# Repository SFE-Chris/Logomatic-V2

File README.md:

Logomatic v2 Serial SD Datalogger (FAT32)
========================================

[  
*Logomatic v2 FAT32(WIG-12772)*](https://www.sparkfun.com/products/12772)

The Logomatic is a great data logger that appears as a flash drive on any operating system. Logs are created
in FAT32 format on the microSD media and can be downloaded quickly over a USB connection by dragging and dropping 
the text files from the device. The board has a built-in RTC and 10 available GPIO pins. 

Repository Contents
-------------------
* **/Firmware** - Firmware that comes pre-installed on the Logomatic
* **/Hardware** - All Eagle design files (.brd, .sch)
* **/Production** - Test bed files and production panel files

Documentation
--------------
* **[Hookup Guide](https://learn.sparkfun.com/tutorials/logomatic-hookup-guide/)** - Basic hookup guide for the Logomatic v2.

Product Versions
----------------
* [WIG-12772](https://www.sparkfun.com/products/12772)- Logomatic v2 with micro-B USB connector and FAT32 programming. 
* *[WIG-10216 (RETIRED)](https://www.sparkfun.com/products/10216)- Logomatic v2 with mini-B USB connector and FAT16 programming.*

License Information
-------------------
The hardware is released under [Creative Commons ShareAlike 4.0 International](https://creativecommons.org/licenses/by-sa/4.0/).
The code is beerware; if you see me (or any other SparkFun employee) at the local, and you've found our code helpful, please buy us a round!

Distributed as-is; no warranty is given.

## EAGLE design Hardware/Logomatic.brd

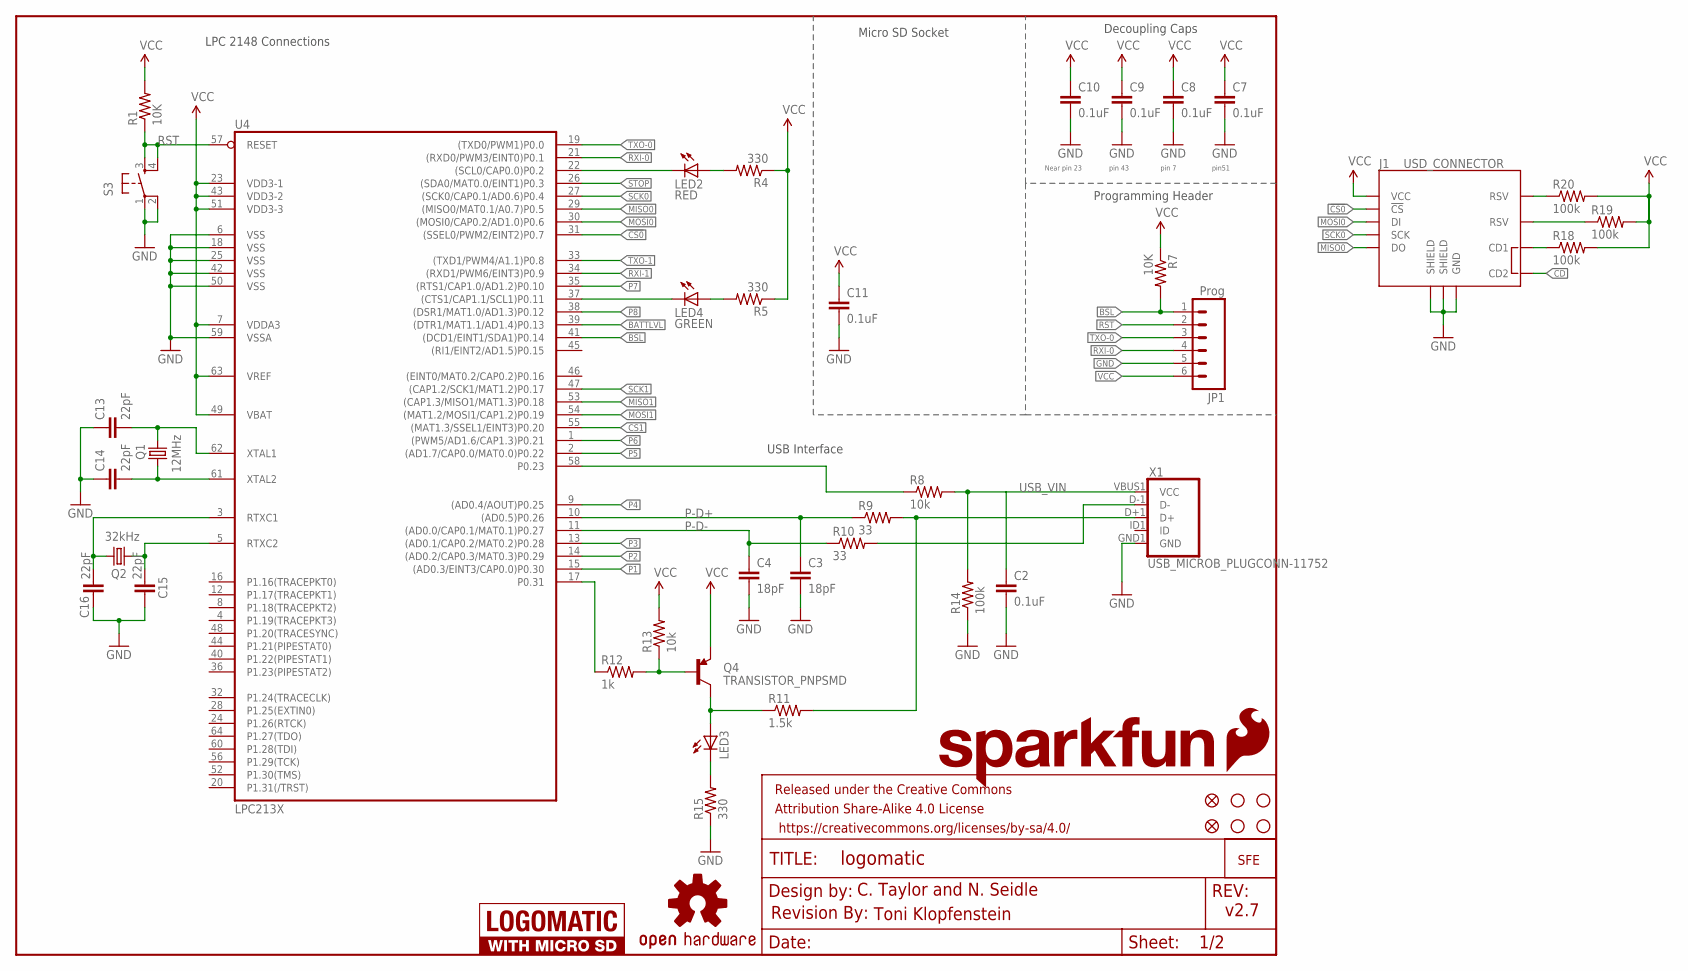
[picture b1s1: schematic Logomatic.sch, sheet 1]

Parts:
C2, C7, C8, C9, C10, C11: 0.1uF; 0603-CAP
C3, C4: 18pF; 0603-CAP
C13, C14, C15, C16: 22pF; 0603-CAP
FRAME2: FRAME-LETTER; CREATIVE_COMMONS
J1: USD_CONNECTOR; MICRO-SD-SOCKET-PP
JP1: Prog; 1X06
LED2: RED; LED-0603
LED3: LED-RED0603; LED-0603
LED4: GREEN; LED-0603
LOGO1: OSHW-LOGOL; OSHW-LOGO-L
LOGO2: SFE_LOGO_NAME.1_INCH; SFE_LOGO_NAME_.1
LOGO3: SFE_LOGO_FLAME.4_INCH; SFE_LOGO_FLAME_.4
Q1: 12MHz; CRYSTAL-SMD-5X3
Q2: 32kHz; CRYSTAL-32KHZ-SMD
Q4: TRANSISTOR_PNPSMD; SOT23-3
R1, R7: 10K; 0603-RES@1
R4, R5, R15: 330; 0603-RES
R8, R13: 10k; 0603-RES@1
R9, R10: 33; 0603-RES
R11: 1.5k; 0603
R12: 1k; 0603-RES@1
R14: 100k; 0603-RES@1
R18, R19, R20: 100k; 0603-RES
S3: Reset; TACTILE_SWITCH_SMD
U4: LPC213X; SQFP-S-10X10-64
U$1, U$2: FIDUCIAL1X2; FIDUCIAL-1X2
U$3, U$4, U$5, U$8: STAND-OFF
U$6: LOGOMATIC_LOGO
U$7: LOGO-SFESK; SFE-LOGO-FLAME
U$10: REVISION
X1: USB_MICROB_PLUGCONN-11752; USB-B-MICRO-SMD_V03

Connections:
!CS0: J1.CS (!CS), U4.31 ((SSEL0/PWM2/EINT2)P0.7)
BATTLVL: U4.39 ((DTR1/MAT1.1/AD1.4)P0.13); also elsewhere on the board
BSL: JP1.1, R7.2, U4.41 ((DCD1/EINT1/SDA1)P0.14)
CD: J1.CD2
CS1: U4.55 ((MAT1.3/SSEL1/EINT3)P0.20); also elsewhere on the board
GND: C2.2, C3.2, C4.2, C7.2, C8.2, C9.2, C10.2, C11.2, C13.1, C14.1, C15.1, C16.1, J1.GND, J1.GND1 (SHIELD), J1.GND3 (SHIELD), JP1.5, R14.1, R15.1, S3.1, S3.2, U4.6 (VSS), U4.18 (VSS), U4.25 (VSS), U4.42 (VSS), U4.50 (VSS), U4.59 (VSSA), X1.GND1 (GND); also elsewhere on the board
MISO0: J1.DO, U4.29 ((MISO0/MAT0.1/A0.7)P0.5)
MISO1: U4.53 ((CAP1.3/MISO1/MAT1.3)P0.18); also elsewhere on the board
MOSI0: J1.DI, U4.30 ((MOSI0/CAP0.2/AD1.0)P0.6)
MOSI1: U4.54 ((MAT1.2/MOSI1/CAP1.2)P0.19); also elsewhere on the board
unnamed: J1.CD1, R18.1
unnamed: J1.RSV1 (RSV), R20.1
unnamed: C13.2, Q1.3 (2), U4.62 (XTAL1)
unnamed: C16.2, Q2.X2 (2), U4.3 (RTXC1)
unnamed: LED2.A, R4.2
unnamed: C15.2, Q2.X1 (1), U4.5 (RTXC2)
unnamed: J1.RSV2 (RSV), R19.1
unnamed: R8.1, U4.58 (P0.23)
unnamed: Q4.1 (B), R12.2, R13.1
unnamed: LED4.A, R5.2
unnamed: C14.2, Q1.1, U4.61 (XTAL2)
unnamed: R12.1, U4.17 (P0.31)
unnamed: LED3.C, R15.2
P1: U4.15 ((AD0.3/EINT3/CAP0.0)P0.30); also elsewhere on the board
P2: U4.14 ((AD0.2/CAP0.3/MAT0.3)P0.29); also elsewhere on the board
P3: U4.13 ((AD0.1/CAP0.2/MAT0.2)P0.28); also elsewhere on the board
P4: U4.9 ((AD0.4/AOUT)P0.25); also elsewhere on the board
P5: U4.2 ((AD1.7/CAP0.0/MAT0.0)P0.22); also elsewhere on the board
P6: U4.1 ((PWM5/AD1.6/CAP1.3)P0.21); also elsewhere on the board
P7: U4.35 ((RTS1/CAP1.0/AD1.2)P0.10); also elsewhere on the board
P8: U4.38 ((DSR1/MAT1.0/AD1.3)P0.12); also elsewhere on the board
P-D+: C3.1, R9.1, U4.10 ((AD0.5)P0.26)
P-D-: C4.1, R10.1, U4.11 ((AD0.0/CAP0.1/MAT0.1)P0.27)
RST: JP1.2, R1.1, S3.3, S3.4, U4.57 (RESET)
RXI-0: JP1.4, U4.21 ((RXD0/PWM3/EINT0)P0.1)
RXI-1: U4.34 ((RXD1/PWM6/EINT3)P0.9); also elsewhere on the board
SCK0: J1.SCLK (SCK), U4.27 ((SCK0/CAP0.1/AD0.6)P0.4)
SCK1: U4.47 ((CAP1.2/SCK1/MAT1.2)P0.17); also elsewhere on the board
STAT: LED3.A, Q4.3 (C), R11.1
STAT0: LED2.C, U4.22 ((SCL0/CAP0.0)P0.2)
STAT1: LED4.C, U4.37 ((CTS1/CAP1.1/SCL1)P0.11)
STOP: U4.26 ((SDA0/MAT0.0/EINT1)P0.3); also elsewhere on the board
TXO-0: JP1.3, U4.19 ((TXD0/PWM1)P0.0)
TXO-1: U4.33 ((TXD1/PWM4/A1.1)P0.8); also elsewhere on the board
USB_D+: R9.2, R11.2, X1.D+1 (D+)
USB_D-: R10.2, X1.D-1 (D-)
USB_VIN: C2.1, R8.2, R14.2, X1.VBUS1 (VCC); also elsewhere on the board
VCC: C7.1, C8.1, C9.1, C10.1, C11.1, J1.VCC, JP1.6, Q4.2 (E), R1.2, R4.1, R5.1, R7.1, R13.2, R18.2, R19.2, R20.2, U4.7 (VDDA3), U4.23 (VDD3-1), U4.43 (VDD3-2), U4.49 (VBAT), U4.51 (VDD3-3), U4.63 (VREF); also elsewhere on the board

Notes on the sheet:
Near pin 23
pin 43
pin51
Decoupling Caps
Programming Header
USB Interface
Micro SD Socket
pin 7
LPC 2148 Connections
C. Taylor and N. Seidle
Toni Klopfenstein
v2.7

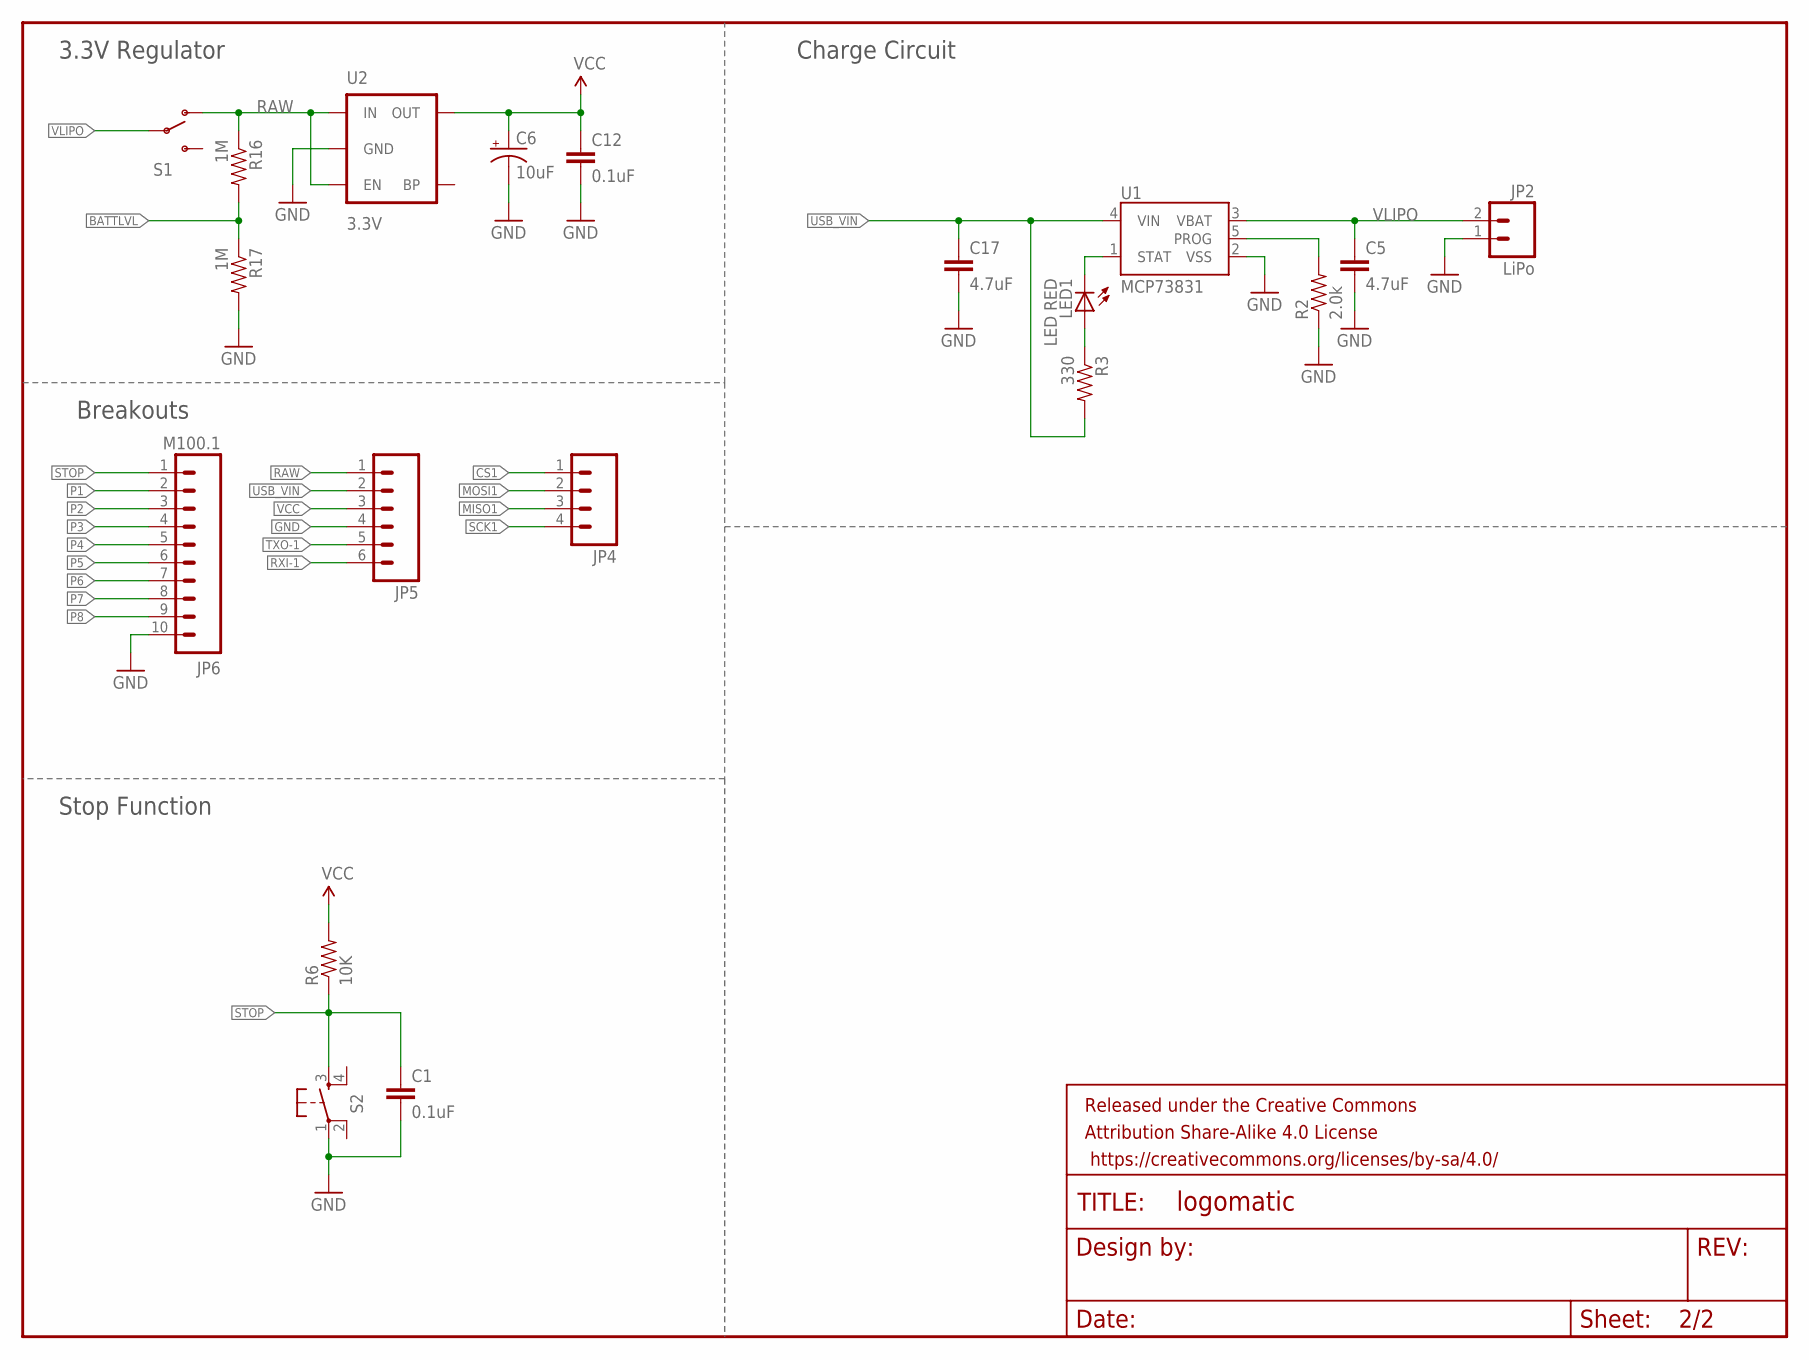
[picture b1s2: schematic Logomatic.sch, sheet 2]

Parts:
C1, C12: 0.1uF; 0603-CAP
C5, C17: 4.7uF; 0603-CAP
C6: 10uF; EIA3216
FRAME4: FRAME-LETTER; CREATIVE_COMMONS
JP2: LiPo; JST-2-SMD
JP4: M04PTH; 1X04
JP5: M06SIP; 1X06
JP6: M100.1; 1X10
LED1: LED RED; LED-0603
R2: 2.0k; 0603-RES
R3: 330; 0603-RES
R6: 10K; 0603-RES@1
R16, R17: 1M; 0603-RES@1
S1: SWITCH-SPSTSMD; AYZ0202
S2: Stop; TACTILE_SWITCH_SMD
U1: MCP73831; SOT23-5
U2: 3.3V; SOT23-5

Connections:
BATTLVL: R16.2, R17.1; also elsewhere on the board
CS1: JP4.1; also elsewhere on the board
GND: C1.2, C5.2, C6.C (-), C12.2, C17.2, JP2.1, JP5.4, JP6.10, R2.1, R17.2, S2.1, U1.2 (VSS), U2.2 (GND); also elsewhere on the board
MISO1: JP4.3; also elsewhere on the board
MOSI1: JP4.2; also elsewhere on the board
unnamed: R2.2, U1.5 (PROG)
unnamed: LED1.C, U1.1 (STAT)
unnamed: LED1.A, R3.1
P1: JP6.2; also elsewhere on the board
P2: JP6.3; also elsewhere on the board
P3: JP6.4; also elsewhere on the board
P4: JP6.5; also elsewhere on the board
P5: JP6.6; also elsewhere on the board
P6: JP6.7; also elsewhere on the board
P7: JP6.8; also elsewhere on the board
P8: JP6.9; also elsewhere on the board
RAW: JP5.1, R16.1, S1.1 (O), U2.1 (IN), U2.3 (EN)
RXI-1: JP5.6; also elsewhere on the board
SCK1: JP4.4; also elsewhere on the board
STOP: C1.1, JP6.1, R6.1, S2.3; also elsewhere on the board
TXO-1: JP5.5; also elsewhere on the board
USB_VIN: C17.1, JP5.2, R3.2, U1.4 (VIN); also elsewhere on the board
VCC: C6.A (+), C12.1, JP5.3, R6.2, U2.5 (OUT); also elsewhere on the board
VLIPO: C5.1, JP2.2, S1.2, U1.3 (VBAT)

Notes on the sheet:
3.3V Regulator
Charge Circuit
Breakouts
Stop Function

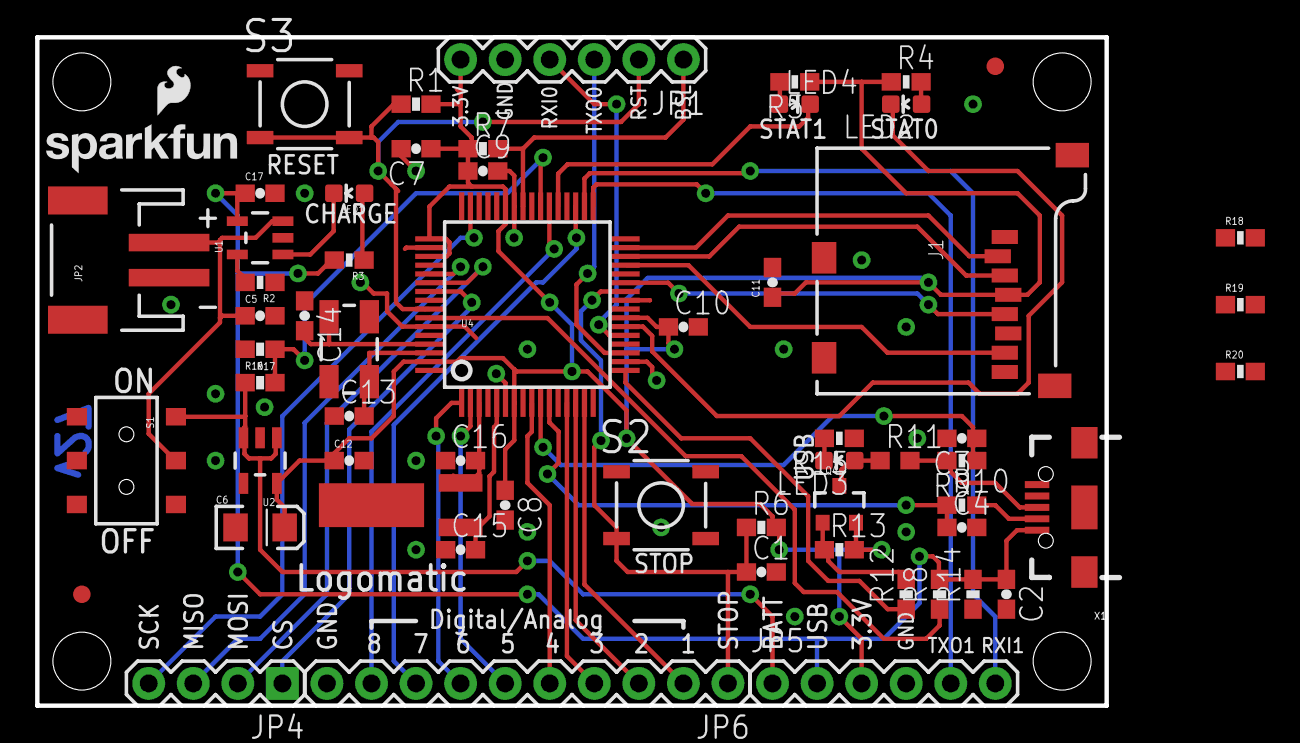
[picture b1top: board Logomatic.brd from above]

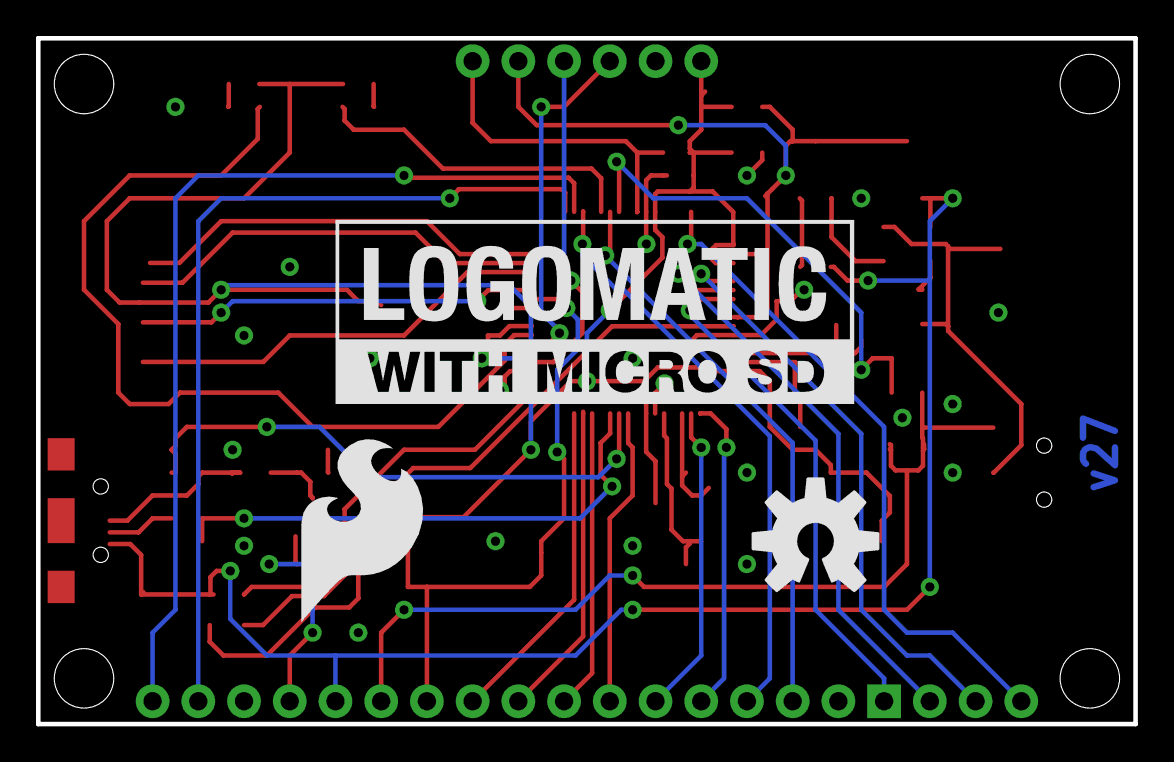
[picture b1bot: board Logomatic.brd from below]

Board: 2 copper layers, 61.0 x 38.1 mm, 71 parts (3 on the bottom side), 52 nets.

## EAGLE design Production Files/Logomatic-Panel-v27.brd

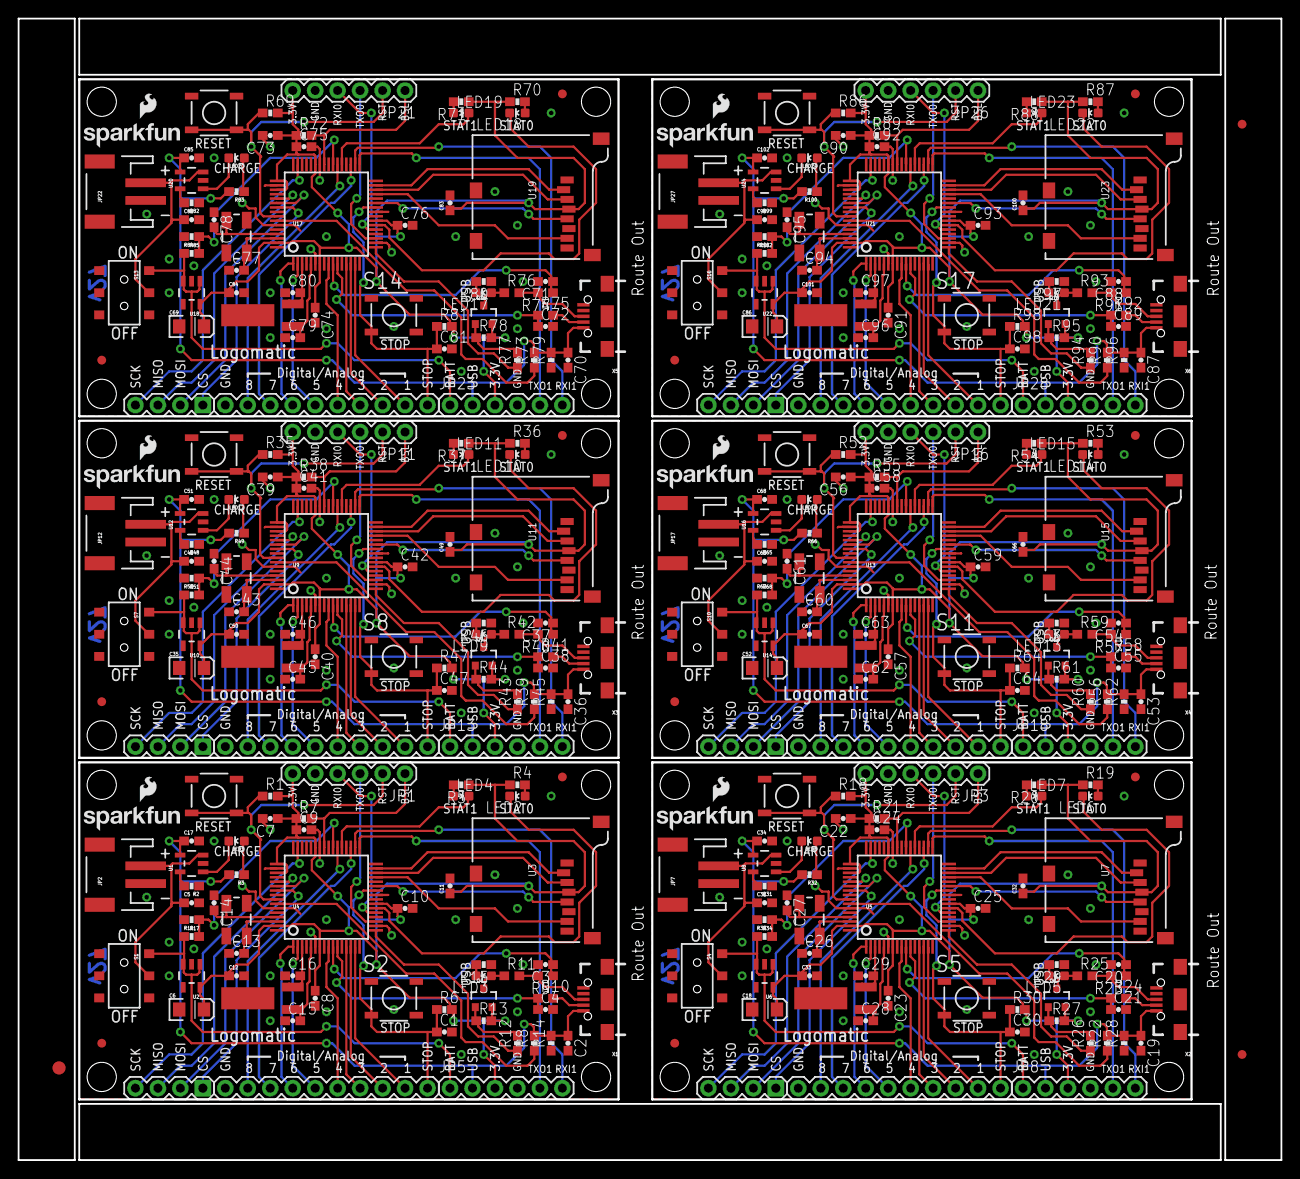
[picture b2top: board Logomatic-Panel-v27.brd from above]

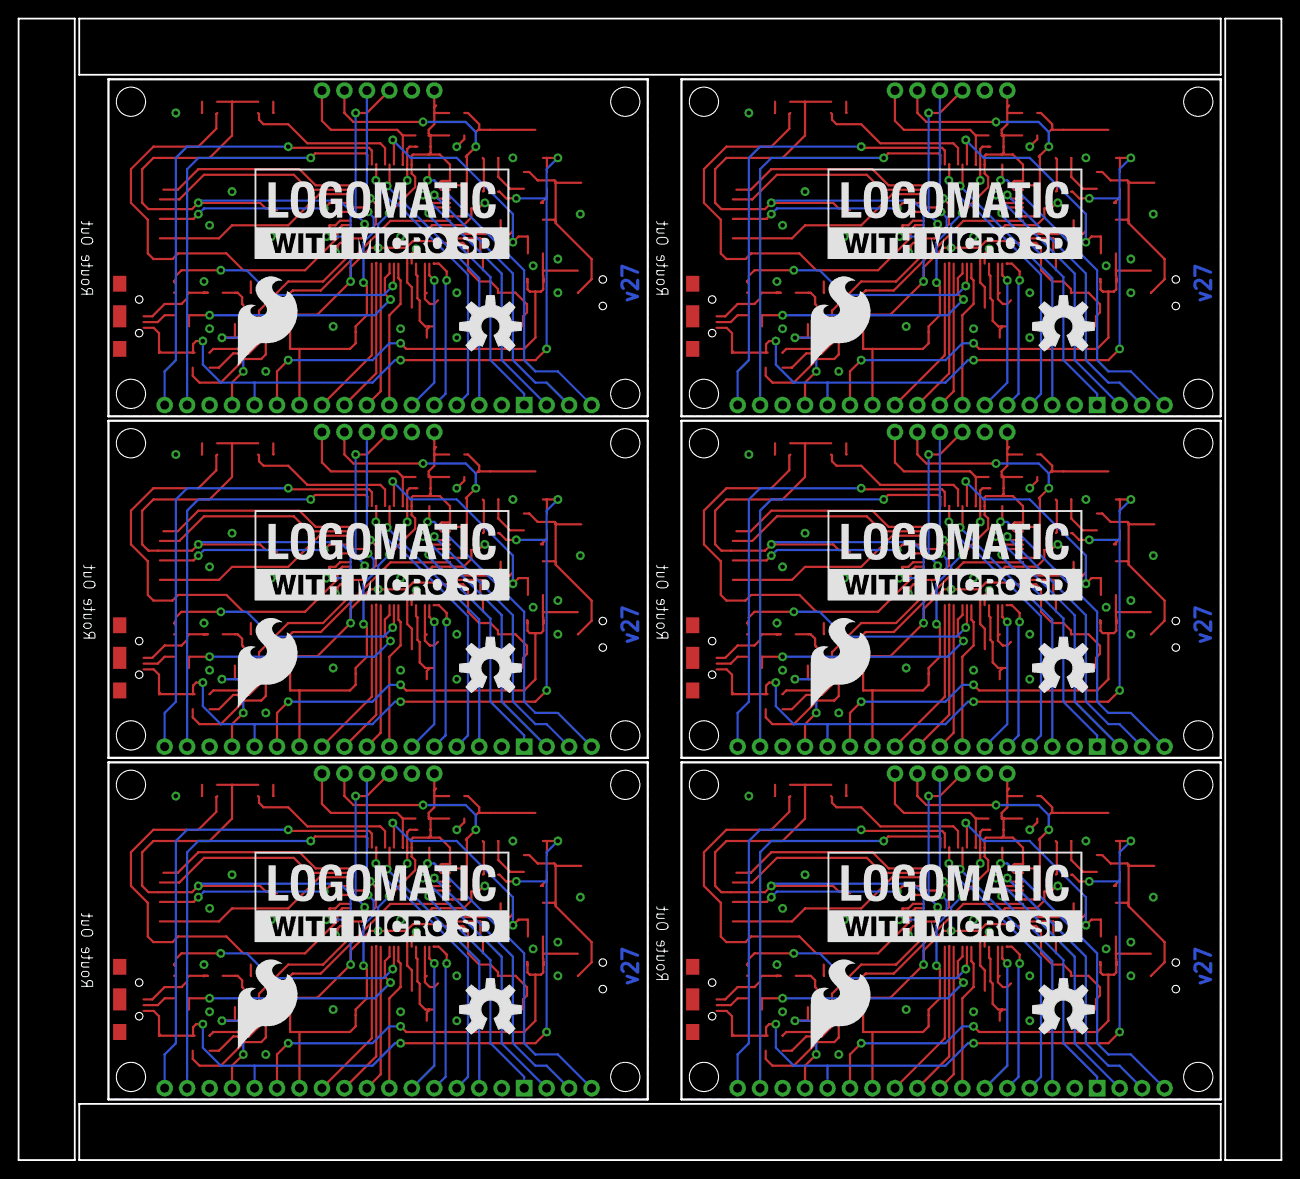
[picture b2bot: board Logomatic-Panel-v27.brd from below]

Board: 2 copper layers, 142.7 x 129.0 mm, 393 parts (18 on the bottom side), 294 nets.

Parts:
C1, C2, C7, C8, C9, C10, C11, C12, C19, C22, C23, C24, C25, C30, C32, C33, C36, C39, C40, C41, C42, C47, C49, C50, C53, C56, C57, C58, C59, C64, C66, C67, C70, C73, C74, C75, C76, C81, C83, C84, C87, C90, C91, C92, C93, C98, C100, C101: 0.1uF; 0603-CAP
C3, C4, C20, C21, C37, C38, C54, C55, C71, C72, C88, C89: 18pF; 0603-CAP
C5, C17, C31, C34, C48, C51, C65, C68, C82, C85, C99, C102: 4.7uF; 0603-CAP
C6, C18, C35, C52, C69, C86: 10uF; EIA3216
C13, C14, C15, C16, C26, C27, C28, C29, C43, C44, C45, C46, C60, C61, C62, C63, C77, C78, C79, C80, C94, C95, C96, C97: 22pF; 0603-CAP
E$1, E$2: FIDUCIAL-1X2
E$3: FIDUCIAL-1.5X3
JP1, JP3, JP11, JP16, JP21, JP26: Prog; 1X06
JP2, JP7, JP12, JP17, JP22, JP27: LiPo; JST-2-SMD
JP4, JP9, JP14, JP19, JP24, JP29: 1X04
JP5, JP8, JP13, JP18, JP23, JP28: 1X06
JP6, JP10, JP15, JP20, JP25, JP30: M100.1; 1X10
LED1, LED8, LED12, LED16, LED20, LED24: LED RED; LED-0603
LED2, LED6, LED10, LED14, LED18, LED22: RED; LED-0603
LED3, LED5, LED9, LED13, LED17, LED21: LED-0603
LED4, LED7, LED11, LED15, LED19, LED23: GREEN; LED-0603
LOGO1, LOGO4, LOGO7, LOGO10, LOGO13, LOGO16: OSHW-LOGOL; OSHW-LOGO-L
LOGO2, LOGO5, LOGO8, LOGO11, LOGO14, LOGO17: SFE_LOGO_NAME.1_INCH; SFE_LOGO_NAME_.1
LOGO3, LOGO6, LOGO9, LOGO12, LOGO15, LOGO18: SFE_LOGO_FLAME.4_INCH; SFE_LOGO_FLAME_.4
Q1, Q3, Q7, Q10, Q13, Q16: 12MHz; CRYSTAL-SMD-5X3
Q2, Q5, Q8, Q11, Q14, Q17: 32kHz; CRYSTAL-32KHZ-SMD
Q4, Q6, Q9, Q12, Q15, Q18: TRANSISTOR_PNPSMD; SOT23-3
R1, R6, R7, R18, R21, R30, R35, R38, R47, R52, R55, R64, R69, R72, R81, R86, R89, R98: 10K; 0603-RES
R2, R31, R48, R65, R82, R99: 2K; 0603-RES
R3, R4, R5, R15, R19, R20, R29, R32, R36, R37, R46, R49, R53, R54, R63, R66, R70, R71, R80, R83, R87, R88, R97, R100: 330; 0603-RES
R8, R13, R22, R27, R39, R44, R56, R61, R73, R78, R90, R95: 10k; 0603-RES
R9, R10, R23, R24, R40, R41, R57, R58, R74, R75, R91, R92: 33; 0603
R11, R25, R42, R59, R76, R93: 1.5k; 0603
R12, R26, R43, R60, R77, R94: 1k; 0603-RES
R14, R28, R45, R62, R79, R96: 100k; 0603-RES
R16, R17, R33, R34, R50, R51, R67, R68, R84, R85, R101, R102: 1M; 0603-RES
S1, S4, S7, S10, S13, S16: AYZ0202
S2, S5, S8, S11, S14, S17: Stop; TACTILE_SWITCH_SMD
S3, S6, S9, S12, S15, S18: Reset; TACTILE_SWITCH_SMD
U1, U8, U12, U16, U20, U24: MCP73831; SOT23-5
U2, U6, U10, U14, U18, U22: 3.3V; SOT23-5
U3, U7, U11, U15, U19, U23: USD-SOCKETNEW; MICRO-SD-SOCKET-PP
U4, U5, U9, U13, U17, U21: LPC213X; SQFP-S-10X10-64
U$1, U$2, U$9, U$10, U$17, U$18, U$25, U$26, U$33, U$34, U$41, U$42: FIDUCIAL1X2; FIDUCIAL-1X2
U$3, U$4, U$5, U$8, U$11, U$12, U$13, U$14, U$19, U$20, U$21, U$22, U$27, U$28, U$29, U$30, U$35, U$36, U$37, U$38, U$43, U$44, U$45, U$46: STAND-OFF
U$6, U$16, U$24, U$32, U$40, U$48: LOGOMATIC_LOGO
U$7, U$15, U$23, U$31, U$39, U$47: LOGO-SFESK; SFE-LOGO-FLAME
X1, X2, X3, X4, X5, X6: USB_MICROB_PLUGCONN-11752; USB-B-MICRO-SMD_V03

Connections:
BATTLVL: R16.2, R17.1, U4.39
BATTLVL1: R33.2, R34.1, U5.39
BATTLVL2: R50.2, R51.1, U9.39
BATTLVL3: R67.2, R68.1, U13.39
BATTLVL4: R84.2, R85.1, U17.39
BATTLVL5: R101.2, R102.1, U21.39
BSL: JP1.1, R7.2, U4.41
BSL1: JP3.1, R21.2, U5.41
BSL2: JP11.1, R38.2, U9.41
BSL3: JP16.1, R55.2, U13.41
BSL4: JP21.1, R72.2, U17.41
BSL5: JP26.1, R89.2, U21.41
CS0: U3.2, U4.31
CS1: JP4.1, U4.55
CS2: U5.31, U7.2
CS3: JP9.1, U5.55
CS4: U9.31, U11.2
CS5: JP14.1, U9.55
CS6: U13.31, U15.2
CS7: JP19.1, U13.55
CS8: U17.31, U19.2
CS9: JP24.1, U17.55
CS10: U21.31, U23.2
CS11: JP29.1, U21.55
GND: C1.2, C2.2, C3.2, C4.2, C5.2, C6.C, C7.2, C8.2, C9.2, C10.2, C11.2, C12.2, C13.1, C14.1, C15.1, C16.1, C17.2, JP1.5, JP2.1, JP5.4, JP6.10, R2.1, R14.1, R15.1, R17.2, S2.1, S3.1, S3.2, U1.2, U2.2, U3.6, U3.CD2, U3.GND1, U4.6, U4.18, U4.25, U4.42, U4.50, U4.59, X1.GND1
GND1: C18.C, C19.2, C20.2, C21.2, C22.2, C23.2, C24.2, C25.2, C26.1, C27.1, C28.1, C29.1, C30.2, C31.2, C32.2, C33.2, C34.2, JP3.5, JP7.1, JP8.4, JP10.10, R28.1, R29.1, R31.1, R34.2, S5.1, S6.1, S6.2, U5.6, U5.18, U5.25, U5.42, U5.50, U5.59, U6.2, U7.6, U7.CD2, U7.GND1, U8.2, X2.GND1
GND2: C35.C, C36.2, C37.2, C38.2, C39.2, C40.2, C41.2, C42.2, C43.1, C44.1, C45.1, C46.1, C47.2, C48.2, C49.2, C50.2, C51.2, JP11.5, JP12.1, JP13.4, JP15.10, R45.1, R46.1, R48.1, R51.2, S8.1, S9.1, S9.2, U9.6, U9.18, U9.25, U9.42, U9.50, U9.59, U10.2, U11.6, U11.CD2, U11.GND1, U12.2, X3.GND1
GND3: C52.C, C53.2, C54.2, C55.2, C56.2, C57.2, C58.2, C59.2, C60.1, C61.1, C62.1, C63.1, C64.2, C65.2, C66.2, C67.2, C68.2, JP16.5, JP17.1, JP18.4, JP20.10, R62.1, R63.1, R65.1, R68.2, S11.1, S12.1, S12.2, U13.6, U13.18, U13.25, U13.42, U13.50, U13.59, U14.2, U15.6, U15.CD2, U15.GND1, U16.2, X4.GND1
GND4: C69.C, C70.2, C71.2, C72.2, C73.2, C74.2, C75.2, C76.2, C77.1, C78.1, C79.1, C80.1, C81.2, C82.2, C83.2, C84.2, C85.2, JP21.5, JP22.1, JP23.4, JP25.10, R79.1, R80.1, R82.1, R85.2, S14.1, S15.1, S15.2, U17.6, U17.18, U17.25, U17.42, U17.50, U17.59, U18.2, U19.6, U19.CD2, U19.GND1, U20.2, X5.GND1
GND5: C86.C, C87.2, C88.2, C89.2, C90.2, C91.2, C92.2, C93.2, C94.1, C95.1, C96.1, C97.1, C98.2, C99.2, C100.2, C101.2, C102.2, JP26.5, JP27.1, JP28.4, JP30.10, R96.1, R97.1, R99.1, R102.2, S17.1, S18.1, S18.2, U21.6, U21.18, U21.25, U21.42, U21.50, U21.59, U22.2, U23.6, U23.CD2, U23.GND1, U24.2, X6.GND1
MISO0: U3.7, U4.29
MISO1: JP4.3, U4.53
MISO2: U5.29, U7.7
MISO3: JP9.3, U5.53
MISO4: U9.29, U11.7
MISO5: JP14.3, U9.53
MISO6: U13.29, U15.7
MISO7: JP19.3, U13.53
MISO8: U17.29, U19.7
MISO9: JP24.3, U17.53
MISO10: U21.29, U23.7
MISO11: JP29.3, U21.53
MOSI0: U3.3, U4.30
MOSI1: JP4.2, U4.54
MOSI2: U5.30, U7.3
MOSI3: JP9.2, U5.54
MOSI4: U9.30, U11.3
MOSI5: JP14.2, U9.54
MOSI6: U13.30, U15.3
MOSI7: JP19.2, U13.54
MOSI8: U17.30, U19.3
MOSI9: JP24.2, U17.54
MOSI10: U21.30, U23.3
MOSI11: JP29.2, U21.54
unnamed: R2.2, U1.5
unnamed: R22.1, U5.58
unnamed: Q6.1, R26.2, R27.1
unnamed: R26.1, U5.17
unnamed: C13.2, Q1.3, U4.62
unnamed: C16.2, Q2.X2, U4.3
unnamed: LED2.A, R4.2
unnamed: LED5.C, R29.2
unnamed: C15.2, Q2.X1, U4.5
unnamed: LED6.A, R19.2
unnamed: LED7.A, R20.2
unnamed: LED1.C, U1.1
unnamed: LED1.A, R3.1
unnamed: C26.2, Q3.3, U5.62
unnamed: C27.2, Q3.1, U5.61
unnamed: R8.1, U4.58
unnamed: Q4.1, R12.2, R13.1
unnamed: C29.2, Q5.X2, U5.3
unnamed: LED4.A, R5.2
unnamed: C28.2, Q5.X1, U5.5
unnamed: C14.2, Q1.1, U4.61
unnamed: LED8.C, U8.1
unnamed: LED8.A, R32.1
unnamed: R31.2, U8.5
unnamed: R39.1, U9.58
unnamed: Q9.1, R43.2, R44.1
unnamed: R43.1, U9.17
unnamed: LED9.C, R46.2
unnamed: LED10.A, R36.2
unnamed: LED11.A, R37.2
unnamed: R12.1, U4.17
unnamed: C43.2, Q7.3, U9.62
unnamed: LED3.C, R15.2
unnamed: C44.2, Q7.1, U9.61
unnamed: C46.2, Q8.X2, U9.3
unnamed: C45.2, Q8.X1, U9.5
unnamed: LED12.C, U12.1
unnamed: LED12.A, R49.1
unnamed: R48.2, U12.5
unnamed: R56.1, U13.58
unnamed: Q12.1, R60.2, R61.1
unnamed: R60.1, U13.17
unnamed: LED13.C, R63.2
unnamed: LED14.A, R53.2
unnamed: LED15.A, R54.2
unnamed: C60.2, Q10.3, U13.62
unnamed: C61.2, Q10.1, U13.61
unnamed: C63.2, Q11.X2, U13.3
unnamed: C62.2, Q11.X1, U13.5
unnamed: LED16.C, U16.1
unnamed: LED16.A, R66.1
unnamed: R65.2, U16.5
unnamed: R73.1, U17.58
unnamed: Q15.1, R77.2, R78.1
unnamed: R77.1, U17.17
unnamed: LED17.C, R80.2
unnamed: LED18.A, R70.2
unnamed: LED19.A, R71.2
unnamed: C77.2, Q13.3, U17.62
unnamed: C78.2, Q13.1, U17.61
unnamed: C80.2, Q14.X2, U17.3
unnamed: C79.2, Q14.X1, U17.5
unnamed: LED20.C, U20.1
unnamed: LED20.A, R83.1
unnamed: R82.2, U20.5
unnamed: R90.1, U21.58
unnamed: Q18.1, R94.2, R95.1
unnamed: R94.1, U21.17
unnamed: LED21.C, R97.2
unnamed: LED22.A, R87.2
unnamed: LED23.A, R88.2
unnamed: C94.2, Q16.3, U21.62
unnamed: C95.2, Q16.1, U21.61
unnamed: C97.2, Q17.X2, U21.3
unnamed: C96.2, Q17.X1, U21.5
unnamed: LED24.C, U24.1
unnamed: LED24.A, R100.1
unnamed: R99.2, U24.5
P1: JP6.2, U4.15
P2: JP6.3, U4.14
P3: JP6.4, U4.13
P4: JP6.5, U4.9
P5: JP6.6, U4.2
P6: JP6.7, U4.1
P7: JP6.8, U4.35
P8: JP6.9, U4.38
P9: JP10.5, U5.9
P10: JP10.4, U5.13
P11: JP10.3, U5.14
P12: JP10.2, U5.15
P13: JP10.8, U5.35
P14: JP10.9, U5.38
P15: JP10.7, U5.1
P16: JP10.6, U5.2
P17: JP15.5, U9.9
P18: JP15.4, U9.13
P19: JP15.3, U9.14
P20: JP15.2, U9.15
P21: JP15.8, U9.35
P22: JP15.9, U9.38
P23: JP15.7, U9.1
P24: JP15.6, U9.2
P25: JP20.5, U13.9
P26: JP20.4, U13.13
P27: JP20.3, U13.14
P28: JP20.2, U13.15
P29: JP20.8, U13.35
P30: JP20.9, U13.38
P31: JP20.7, U13.1
P32: JP20.6, U13.2
P33: JP25.5, U17.9
P34: JP25.4, U17.13
P35: JP25.3, U17.14
P36: JP25.2, U17.15
P37: JP25.8, U17.35
P38: JP25.9, U17.38
P39: JP25.7, U17.1
P40: JP25.6, U17.2
P41: JP30.5, U21.9
P42: JP30.4, U21.13
P43: JP30.3, U21.14
P44: JP30.2, U21.15
P45: JP30.8, U21.35
P46: JP30.9, U21.38
P47: JP30.7, U21.1
P48: JP30.6, U21.2
P-D+: C3.1, R9.1, U4.10
P-D+1: C20.1, R23.1, U5.10
P-D+2: C37.1, R40.1, U9.10
P-D+3: C54.1, R57.1, U13.10
P-D+4: C71.1, R74.1, U17.10
P-D+5: C88.1, R91.1, U21.10
P-D-: C4.1, R10.1, U4.11
P-D-1: C21.1, R24.1, U5.11
P-D-2: C38.1, R41.1, U9.11
P-D-3: C55.1, R58.1, U13.11
P-D-4: C72.1, R75.1, U17.11
P-D-5: C89.1, R92.1, U21.11
RAW: JP5.1, R16.1, S1.1, U2.1, U2.3
RAW1: JP8.1, R33.1, S4.1, U6.1, U6.3
RAW2: JP13.1, R50.1, S7.1, U10.1, U10.3
RAW3: JP18.1, R67.1, S10.1, U14.1, U14.3
RAW4: JP23.1, R84.1, S13.1, U18.1, U18.3
RAW5: JP28.1, R101.1, S16.1, U22.1, U22.3
RST: JP1.2, R1.1, S3.3, S3.4, U4.57
RST1: JP3.2, R18.1, S6.3, S6.4, U5.57
RST2: JP11.2, R35.1, S9.3, S9.4, U9.57
RST3: JP16.2, R52.1, S12.3, S12.4, U13.57
RST4: JP21.2, R69.1, S15.3, S15.4, U17.57
RST5: JP26.2, R86.1, S18.3, S18.4, U21.57
RXI-0: JP1.4, U4.21
RXI-1: JP5.6, U4.34
RXI-2: JP3.4, U5.21
RXI-3: JP8.6, U5.34
RXI-4: JP11.4, U9.21
RXI-5: JP13.6, U9.34
RXI-6: JP16.4, U13.21
RXI-7: JP18.6, U13.34
RXI-8: JP21.4, U17.21
RXI-9: JP23.6, U17.34
RXI-10: JP26.4, U21.21
RXI-11: JP28.6, U21.34
SCK0: U3.5, U4.27
SCK1: JP4.4, U4.47
SCK2: U5.27, U7.5
SCK3: JP9.4, U5.47
SCK4: U9.27, U11.5
SCK5: JP14.4, U9.47
SCK6: U13.27, U15.5
SCK7: JP19.4, U13.47
SCK8: U17.27, U19.5
SCK9: JP24.4, U17.47
SCK10: U21.27, U23.5
SCK11: JP29.4, U21.47
STAT: LED3.A, Q4.3, R11.1
STAT0: LED2.C, U4.22
STAT1: LED4.C, U4.37
STAT2: LED6.C, U5.22
STAT3: LED7.C, U5.37
STAT4: LED5.A, Q6.3, R25.1
STAT5: LED10.C, U9.22
STAT6: LED11.C, U9.37
STAT7: LED9.A, Q9.3, R42.1
STAT8: LED14.C, U13.22
STAT9: LED15.C, U13.37
STAT10: LED13.A, Q12.3, R59.1
STAT11: LED18.C, U17.22
STAT12: LED19.C, U17.37
STAT13: LED17.A, Q15.3, R76.1
STAT14: LED22.C, U21.22
STAT15: LED23.C, U21.37
STAT16: LED21.A, Q18.3, R93.1
STOP: C1.1, JP6.1, R6.1, S2.3, U4.26
STOP1: C30.1, JP10.1, R30.1, S5.3, U5.26
STOP2: C47.1, JP15.1, R47.1, S8.3, U9.26
STOP3: C64.1, JP20.1, R64.1, S11.3, U13.26
STOP4: C81.1, JP25.1, R81.1, S14.3, U17.26
STOP5: C98.1, JP30.1, R98.1, S17.3, U21.26
TXO-0: JP1.3, U4.19
TXO-1: JP5.5, U4.33
TXO-2: JP3.3, U5.19
TXO-3: JP8.5, U5.33
TXO-4: JP11.3, U9.19
TXO-5: JP13.5, U9.33
TXO-6: JP16.3, U13.19
TXO-7: JP18.5, U13.33
TXO-8: JP21.3, U17.19
TXO-9: JP23.5, U17.33
TXO-10: JP26.3, U21.19
TXO-11: JP28.5, U21.33
USB_D+: R9.2, R11.2, X1.D+1
USB_D+1: R23.2, R25.2, X2.D+1
USB_D+2: R40.2, R42.2, X3.D+1
USB_D+3: R57.2, R59.2, X4.D+1
USB_D+4: R74.2, R76.2, X5.D+1
USB_D+5: R91.2, R93.2, X6.D+1
USB_D-: R10.2, X1.D-1
USB_D-1: R24.2, X2.D-1
USB_D-2: R41.2, X3.D-1
USB_D-3: R58.2, X4.D-1
USB_D-4: R75.2, X5.D-1
USB_D-5: R92.2, X6.D-1
USB_VIN: C2.1, C17.1, JP5.2, R3.2, R8.2, R14.2, U1.4, X1.VBUS1
USB_VIN1: C19.1, C34.1, JP8.2, R22.2, R28.2, R32.2, U8.4, X2.VBUS1
USB_VIN2: C36.1, C51.1, JP13.2, R39.2, R45.2, R49.2, U12.4, X3.VBUS1
USB_VIN3: C53.1, C68.1, JP18.2, R56.2, R62.2, R66.2, U16.4, X4.VBUS1
USB_VIN4: C70.1, C85.1, JP23.2, R73.2, R79.2, R83.2, U20.4, X5.VBUS1
USB_VIN5: C87.1, C102.1, JP28.2, R90.2, R96.2, R100.2, U24.4, X6.VBUS1
VCC: C6.A, C7.1, C8.1, C9.1, C10.1, C11.1, C12.1, JP1.6, JP5.3, Q4.2, R1.2, R4.1, R5.1, R6.2, R7.1, R13.2, U2.5, U3.4, U4.7, U4.23, U4.43, U4.49, U4.51, U4.63
VCC1: C18.A, C22.1, C23.1, C24.1, C25.1, C32.1, C33.1, JP3.6, JP8.3, Q6.2, R18.2, R19.1, R20.1, R21.1, R27.2, R30.2, U5.7, U5.23, U5.43, U5.49, U5.51, U5.63, U6.5, U7.4
VCC2: C35.A, C39.1, C40.1, C41.1, C42.1, C49.1, C50.1, JP11.6, JP13.3, Q9.2, R35.2, R36.1, R37.1, R38.1, R44.2, R47.2, U9.7, U9.23, U9.43, U9.49, U9.51, U9.63, U10.5, U11.4
VCC3: C52.A, C56.1, C57.1, C58.1, C59.1, C66.1, C67.1, JP16.6, JP18.3, Q12.2, R52.2, R53.1, R54.1, R55.1, R61.2, R64.2, U13.7, U13.23, U13.43, U13.49, U13.51, U13.63, U14.5, U15.4
VCC4: C69.A, C73.1, C74.1, C75.1, C76.1, C83.1, C84.1, JP21.6, JP23.3, Q15.2, R69.2, R70.1, R71.1, R72.1, R78.2, R81.2, U17.7, U17.23, U17.43, U17.49, U17.51, U17.63, U18.5, U19.4
VCC5: C86.A, C90.1, C91.1, C92.1, C93.1, C100.1, C101.1, JP26.6, JP28.3, Q18.2, R86.2, R87.1, R88.1, R89.1, R95.2, R98.2, U21.7, U21.23, U21.43, U21.49, U21.51, U21.63, U22.5, U23.4
VLIPO: C5.1, JP2.2, S1.2, U1.3
VLIPO1: C31.1, JP7.2, S4.2, U8.3
VLIPO2: C48.1, JP12.2, S7.2, U12.3
VLIPO3: C65.1, JP17.2, S10.2, U16.3
VLIPO4: C82.1, JP22.2, S13.2, U20.3
VLIPO5: C99.1, JP27.2, S16.2, U24.3

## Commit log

2010-10-18 ASCII logging at 115200 baud drops packets about every 176144 bytes.
2010-10-18 Added README file
2013-08-22 Repo structure update and adding board files
2013-08-22 More repo clean up
2014-02-19 Version 2.7 board commit
2014-03-10 Updating to fancy new silk on board
2014-04-21 Changing 0603 LED package
2014-04-22 created panel v27
2014-06-30 Updating firmware files and readme for version 2.1
2014-06-30 Update README.md
    Fixing product image links and product page links.
2015-06-24 Defined the buf_size in a single place so that it is easy to change.
2015-11-17 added missing semicolons
2015-11-30 Removed all compiler warnings, added comments, and added header guards to our headers.
2015-12-01 updated the .gitignore file
2015-12-01 syntax fix (missing double-quote)
2015-12-01 moved the target prefix into a variable
2015-12-01 path case fix
2015-12-01 Added comments and missing double quote
2015-12-01 Pulled in more of our standard gitignore
2015-12-02 moved a misplaced C-only warning flag
2015-12-02 constness fixes
2015-12-02 added common Linux backup file suffix to .gitignore
2015-12-05 moved an assignment happening in 'if' and 'else' block behind both
2015-12-05 moved common code into a function
2015-12-05 moved more common code into the new function, removed unnecessary code
2015-12-05 added missing local variable
2015-12-05 added missing initializer for temp_buff
2015-12-05 replaced an unrolled loop with the loop
2015-12-05 added missing 'ind' update
2015-12-05 squeezed pushValue
2015-12-05 moved the polling loops into a function
2015-12-05 style fixes
2015-12-05 moved the result extraction from 'pushValue' into 'sample', removed obsolete comment
2015-12-05 moved the tests into 'sample'
2015-12-05 moved common code into 'sample'
2015-12-05 abstracted common code into a macro
2015-12-05 missing buf_size update
2015-12-07 Sorted gitignore
2015-12-08 Pull request and changed itoa parameters to be more standard
2015-12-09 replaced another 512
2015-12-09 style fix (macros name)
2015-12-09 moved delay_ms into its own files

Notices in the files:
parts and their libraries:
SparkFun-Aesthetics: Licensing: Creative Commons ShareAlike 4.0 International - https://creativecommons.org/licenses/by-sa/4.0
SparkFun-Aesthetics: Released under the Creative Commons Attribution Share-Alike 4.0 License
SparkFun-Aesthetics: Released under the Creative Commons
